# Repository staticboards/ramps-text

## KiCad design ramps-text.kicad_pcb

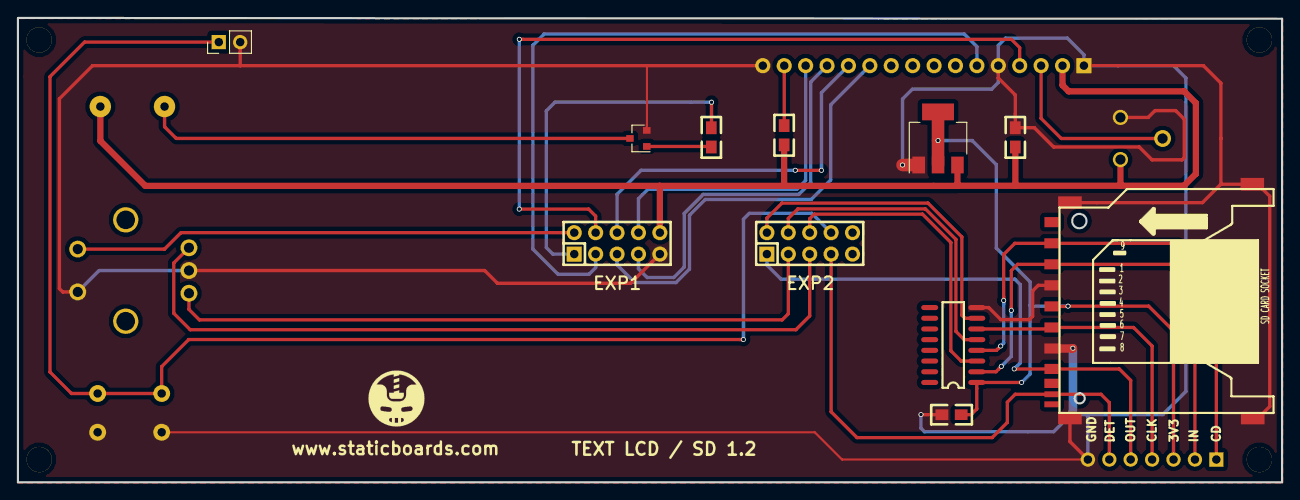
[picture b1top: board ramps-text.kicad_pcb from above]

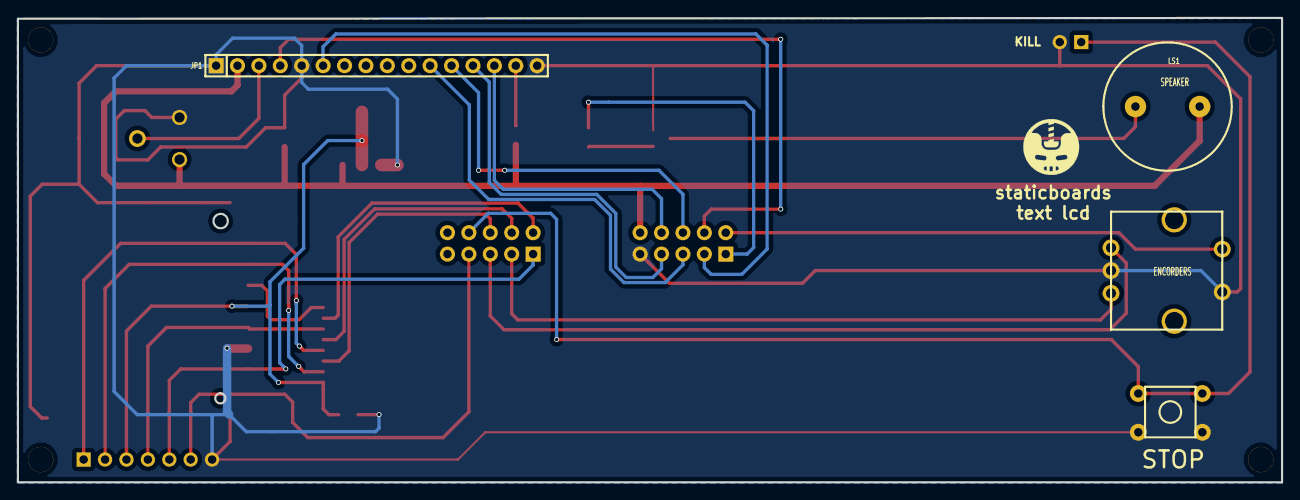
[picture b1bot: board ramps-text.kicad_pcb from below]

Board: 2 copper layers, 150.0 x 55.1 mm, 17 parts (4 on the bottom side), 26 nets.

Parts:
C1, C2: 1u; 0805_1
EXP1: CONN_02X05; IDC-10-1_1
EXP2: CONN_02X05; IDC-10-1_2
IC1: 74HC4050; SO-16_1
IC2: LDO 3.3; SOT-223
J1: CONN_01X07; Pin_Header_Straight_1x07_Pitch2.54mm
J2: KILL; Pin_Header_Straight_1x02_Pitch2.54mm
JP1: DMC204LCD; SIP-16-1_1
JP4: SD_Card; SD-4_1
LS1: Buzzer; RB.3_.6-1_1
LS2: ENCODER; ENCODERS_1
Q1: NPN; SOT-23
R2: 448r; 0805_1
RLED1: 68r; 0805_1
RV1: POT; RES-2_1
SW1: SW_PUSH_2P; SW_6X6MM_ONE_LAYER_1

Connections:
+3V3: C2.1, IC1.1, IC2.2, IC2.4, J1.3, JP4.4
BUZZ: EXP1.1, R2.2
DATAIN: IC1.2, J1.2, JP4.2
DATAOUT: EXP2.1, J1.5, JP4.7
ENCA: EXP2.5, LS2.1
ENCB: EXP2.3, LS2.3
ENCSW: EXP1.2, LS2.5
Earth: C1.2, C2.2, EXP1.9, IC1.8, IC2.1, J1.7, J2.2, JP1.1, JP1.5, JP1.16, JP4.3, JP4.6, JP4.12, JP4.13, LS2.2, LS2.4, Q1.2, RV1.3, SW1.2
INDATAIN: EXP2.6, IC1.3
INSDCD: EXP2.4, IC1.5
INSDCLK: EXP2.2, IC1.7
LCD4: EXP1.5, JP1.11
LCD5: EXP1.6, JP1.12
LCD6: EXP1.7, JP1.13
LCD7: EXP1.8, JP1.14
LCDE: EXP1.3, JP1.6
LCDRS: EXP1.4, JP1.4
unnamed: JP1.15, RLED1.2
unnamed: LS1.2, Q1.3
unnamed: Q1.1, R2.1
RESET: EXP2.8, J2.1, SW1.1
SDCD: IC1.4, J1.1, JP4.1
SDCLK: IC1.6, J1.4, JP4.5
SDDETECT: EXP2.7, J1.6, JP4.10
VCC: C1.1, EXP1.10, IC2.3, JP1.2, LS1.1, RLED1.1, RV1.1
VLCD: JP1.3, RV1.2

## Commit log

2018-11-06 initial
2018-11-08 schematics
2018-11-08 licencia
